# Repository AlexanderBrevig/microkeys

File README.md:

# Microkeys

## Install

* `git clone --recurse-submodules git@github.com:alexanderbrevig/microkeys`
* `make`
* # make your mods

This will generate a stub PCB that I modified to get to the final design.

## REFs

https://splitkb.com/
https://fkcaps.com/?a=FlatFootFox
https://flatfootfox.com/ergogen-introduction/

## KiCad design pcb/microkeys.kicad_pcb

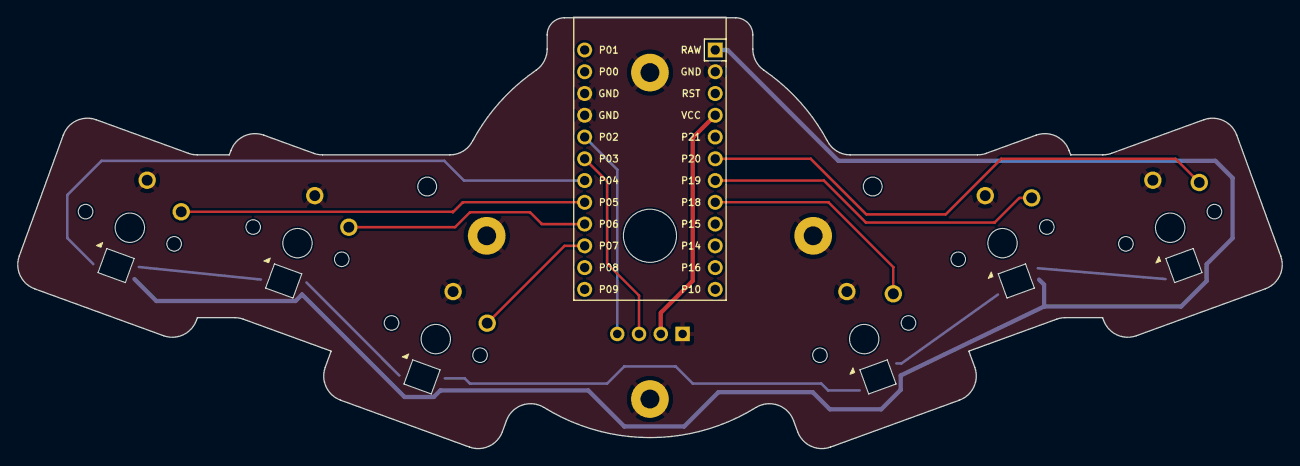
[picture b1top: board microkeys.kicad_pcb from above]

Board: 2 copper layers, 147.6 x 50.3 mm, 14 parts (0 on the bottom side), 17 nets.

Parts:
LED1, LED2, LED3, LED4, LED5, LED6: SK6812MINIE
MCU1: ProMicro
OLED1: OLED; OLED_headers
S1, S2, S3, S4, S5, S6: PG1350

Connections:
GND: LED1.3, LED2.3, LED3.3, LED4.3, LED5.3, LED6.3, MCU1.2, MCU1.15, MCU1.16, OLED1.1, S1.2, S2.2, S3.2, S4.2, S5.2, S6.2
P2: MCU1.17, OLED1.4
P3: MCU1.18, OLED1.3
P4: LED1.4, MCU1.19
P5: MCU1.20, S1.1
P6: MCU1.21, S2.1
P7: MCU1.22, S3.1
P18: MCU1.8, S6.1
P19: MCU1.7, S5.1
P20: MCU1.6, S4.1
RAW: LED1.1, LED2.1, LED3.1, LED4.1, LED5.1, LED6.1, MCU1.1
VCC: MCU1.4, OLED1.2
l_index_dout: LED3.2, LED6.4
l_middle_dout: LED2.2, LED3.4
l_ring_dout: LED1.2, LED2.4
r_index_dout: LED5.4, LED6.2
r_middle_dout: LED4.4, LED5.2

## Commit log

2023-08-16 feat: initial commit, ordered rev 1
2023-08-16 feat: add kicad design
